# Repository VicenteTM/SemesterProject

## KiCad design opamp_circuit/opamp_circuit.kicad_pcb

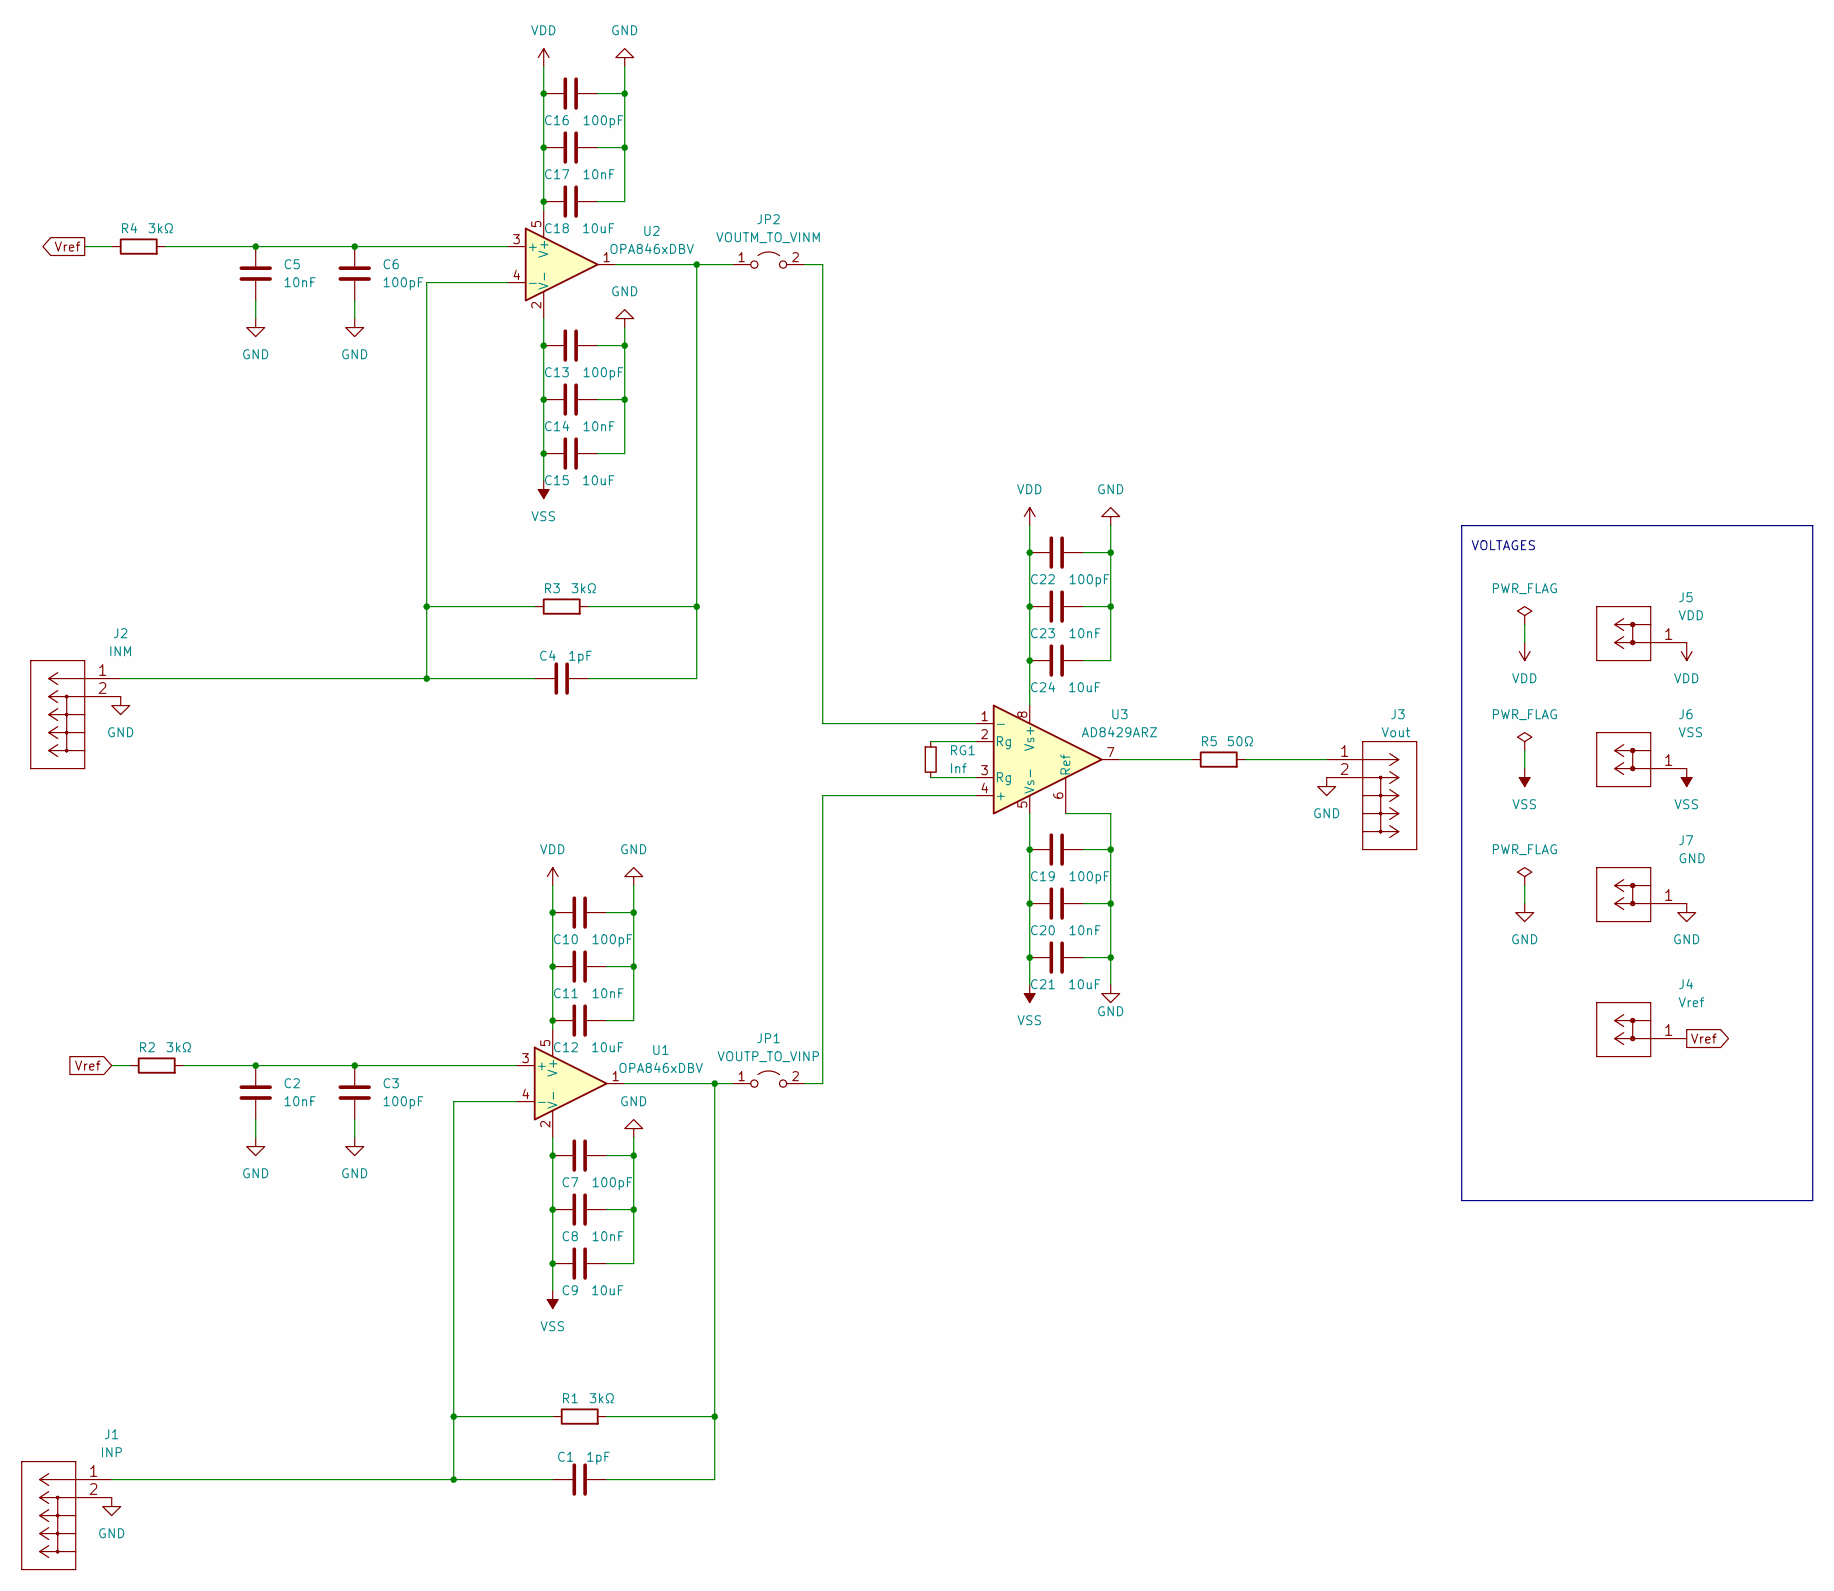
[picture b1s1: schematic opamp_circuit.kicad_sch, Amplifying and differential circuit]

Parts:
C1, C4: 1pF; C_1206_3216Metric
C2, C5, C8, C11, C14, C17, C20, C23: 10nF; C_1206_3216Metric
C3, C6, C7, C10, C13, C16, C19, C22: 100pF; C_1206_3216Metric
C9, C12, C15, C18, C21, C24: 10uF; C1206X106J4RACAUTO
J1: INP; RF2-04A-T-00-50-G
J2: INM; RF2-04A-T-00-50-G
J3: Vout; RF2-04A-T-00-50-G
J4: Vref; 973582101
J5: VDD; 973582101
J6: VSS; 973582101
J7: GND; 973582101
JP1: VOUTP_TO_VINP; BC020-02-A-0200-0300-L-G
JP2: VOUTM_TO_VINM; BC020-02-A-0200-0300-L-G
R1, R2, R3, R4: 3kΩ; R_1206_3216Metric_Pad1.30x1.75mm_HandSolder
R5: 50Ω; WSC251550R00FEA
RG1: Inf; R_1206_3216Metric_Pad1.30x1.75mm_HandSolder
U1, U2: OPA846xDBV; OPA846IDBVT
U3: AD8429ARZ; AD8429ARZ-R7

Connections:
GND: C2.2, C3.2, C5.2, C6.2, C7.2, C8.2, C9.2, C10.2, C11.2, C12.2, C13.2, C14.2, C15.2, C16.2, C17.2, C18.2, C19.2, C20.2, C21.2, C22.2, C23.2, C24.2, J1.2, J2.2, J3.2, J7.1, U3.6 (Ref)
unnamed: C1.1, J1.1, R1.1, U1.4 (-)
unnamed: C1.2, JP1.1 (A), R1.2, U1.1
unnamed: C2.1, C3.1, R2.2, U1.3 (+)
unnamed: C4.1, J2.1, R3.1, U2.4 (-)
unnamed: C4.2, JP2.1 (A), R3.2, U2.1
unnamed: C5.1, C6.1, R4.2, U2.3 (+)
unnamed: J3.1, R5.2
unnamed: JP1.2 (B), U3.4 (+)
unnamed: JP2.2 (B), U3.1 (-)
unnamed: R5.1, U3.7
unnamed: RG1.1, U3.2 (Rg)
unnamed: RG1.2, U3.3 (Rg)
VDD: C10.1, C11.1, C12.1, C16.1, C17.1, C18.1, C22.1, C23.1, C24.1, J5.1, U1.5 (V+), U2.5 (V+), U3.8 (Vs+)
VSS: C7.1, C8.1, C9.1, C13.1, C14.1, C15.1, C19.1, C20.1, C21.1, J6.1, U1.2 (V-), U2.2 (V-), U3.5 (Vs-)
Vref: J4.1, R2.1, R4.1

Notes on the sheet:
VOLTAGES

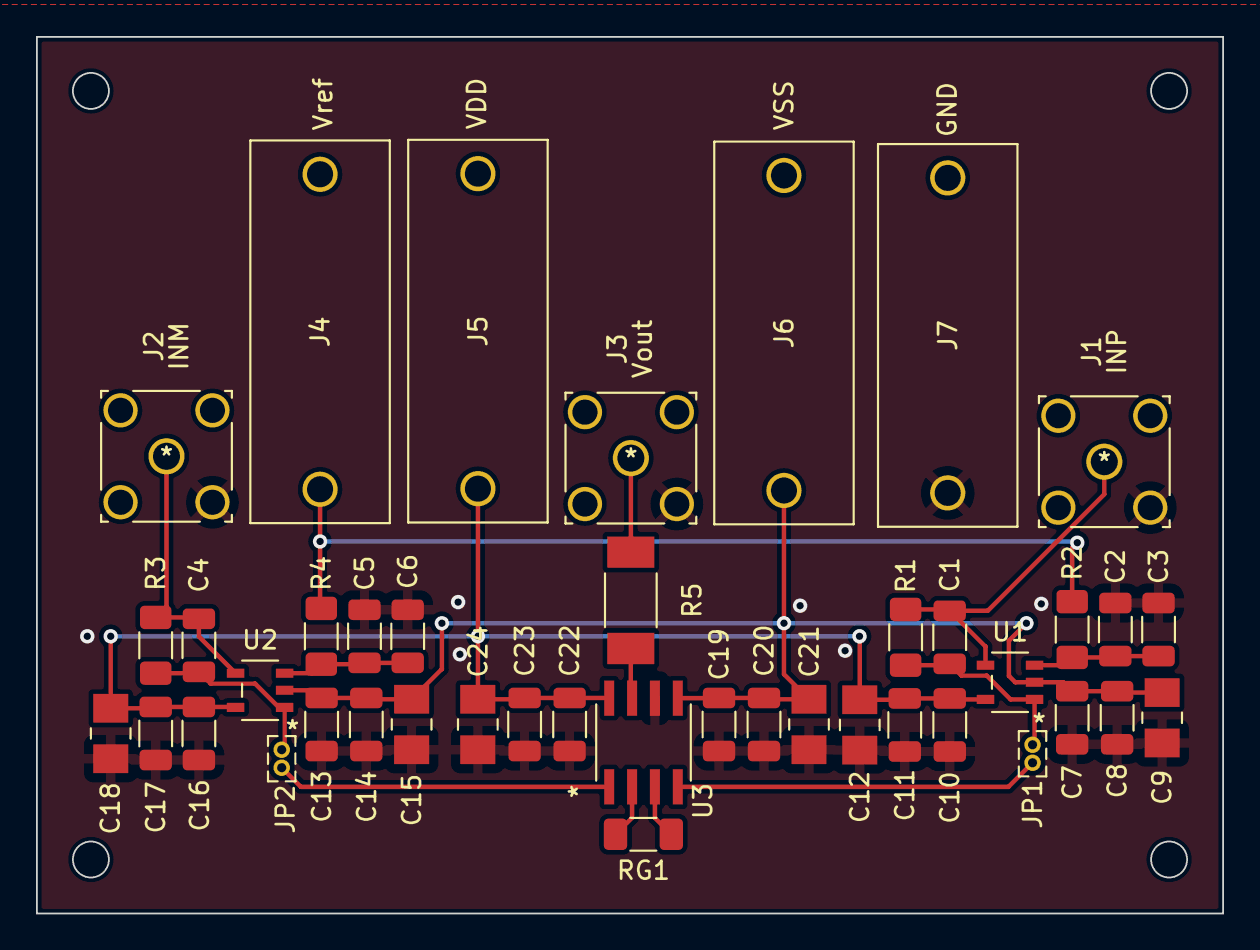
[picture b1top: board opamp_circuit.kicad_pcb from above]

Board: 2 copper layers, 65.9 x 48.7 mm, 42 parts (0 on the bottom side), 16 nets.

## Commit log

2022-11-19 Pcb schematics done starting pcb physical design and noise analysis ltspice
2022-11-22 Version Vicente before advices
2022-11-22 Adjustements after Yassine's advices
2022-11-22 First version pcb. Need to: change cp to same dims and check constraints from the manufacturer
2022-11-24 Better placement and uniform capa, redesign adapting to the instrumentation opamp
2022-11-25 Final design v1
2022-11-25 Renamed capa
2022-11-25 Image circuit
2022-12-05 Post we

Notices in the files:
parts and their libraries:
Copyright 2021 Accelerated Designs. All rights reserved.
